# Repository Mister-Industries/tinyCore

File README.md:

# tinyCore - A Better Way to Learn ESP32

<div align="center">

</div>

ESP32-S3 chips are manufactured by Espressif®.
> Espressif® is a trademark of Espressif Systems (Shanghai) Co.Ltd (https://www.espressif.com/).

The tinyCore ESP32-S3 Board can be programmed with the Arduino® IDE.
> Arduino® is a trademark of Arduino LLC (https://www.arduino.cc/).

## Overview

tinyCore is an engineering learning platform based around an "open-knowledge" microcontroller board designed to help educate individuals on the world of advanced embedded systems. tinyCore’s mission is to bridge the gap between undergrad and industry, equipping young professionals with the resources they need to build their portfolio and bring their ideas to life. 

## Pinout

### Key Features

- **Processor**: ESP32-S3 Mini Dual-Core No-PSRAM
- **Connectivity**: 
  - WiFi & Bluetooth LE
  - USB-C
  - 2x STEMMA/QWIIC I2C Connectors
  - Micro SD Card Slot
  - Built-in LSM6DSO IMU
- **Power**: 
  - USB-C powered
  - LiPo battery support with charging circuit
  - Low power sleep modes, Dedicated I2C PWR Rail
- **Dimensions**: 50mm x 50mm

## Getting Started

Open up the "START-HERE.pdf" document, or check out [our documentation](https://docs.mr.industries) to get started.

## Purchase

If you would like to get a tinyCore for yourself, please [visit our website](https://mr.industries/tiny-core) to purchase one!

For professors, tax-exempt organizations, or bulk orders (>10), please contact us through the following email address:
[support@mr.industries](mailto:support@mr.industries)

## Hardware

The complete hardware design files are available in the [hardware folder](https://github.com/Mister-Industries/tinyCore/tree/main/Hardware), including:
- Schematic files 
- PCB layout files (Altium/KiCad format)
- Bill of Materials (BOM)
- Manufacturing files (Gerber)
- Assembly instructions

## Development

### Contributing

We welcome contributions! Please see our [Contributing Guide](CONTRIBUTING.md) for details on:
- Code style guidelines
- Development workflow
- Testing requirements
- Pull request process

## Community

- [Discord Server](https://discord.gg/hvJZhwfQsF)
- [Bluesky](https://bsky.app/profile/mr.industries)

## License

This project is licensed under the MIT License - see the [LICENSE](LICENSE) file for details.

## Acknowledgments
The tinyCore project thrives thanks to the generous support of our manufacturing and development partners:
### --- PCBWay ---

PCBWay provides exceptional PCB manufacturing services and has been instrumental in bringing tinyCore to life through their reliable prototyping capabilities. You can order our open-source designs directly from [their website](https://www.pcbway.com/project/shareproject/iota_The_Open_Source_Advanced_IoT_Learning_Platform_12776757.html)

Special thanks to:
- The Adafruit team for inspiration
- All of our open source contributors
- "Prof. Eric Bogatin, Prof. Chris Coulston, Tyler Watts, Chaz Havens and countless others who inspired me to create fantastic things." - Geoff M.

## Support

MR.INDUSTRIES offers comprehensive technical support for everyone in our tinyCommunity:

* Help with understanding documentation and setup challenges
* Replacement parts for defective components
* Expert guidance for your tinyCore projects
* Weekly "Office Hours" every Thursday at 4:30 MST on [Discord Server](https://discord.gg/hvJZhwfQsF)
  * Get 1-1 help from our engineers via Discord voice
* Active community support through our [Discord](https://discord.gg/hvJZhwfQsF)

## Star History

You can also send us an email to:
[support@mr.industries](mailto:support@mr.industries)

**Our team is committed to helping you succeed with your project every step of the way.**

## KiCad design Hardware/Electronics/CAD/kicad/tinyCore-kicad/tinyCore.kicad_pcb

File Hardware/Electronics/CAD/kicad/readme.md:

These files were automatically created by Kicad import from the orginal Altium project

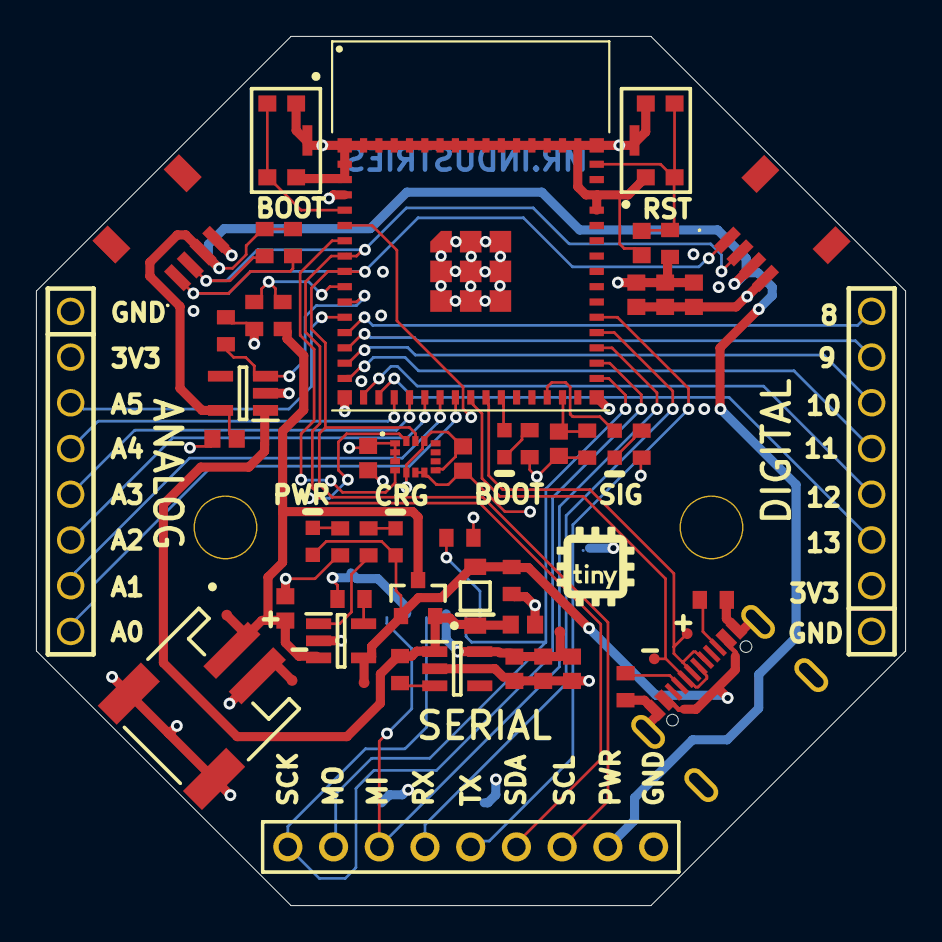
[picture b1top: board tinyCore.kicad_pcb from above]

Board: 4 copper layers, 48.3 x 48.3 mm, 57 parts (1 on the bottom side), 45 nets.

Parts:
B1: LSM6DS3TR
B2, B4: AP2112K-3.3TRG1; SOT95P270X145-5N
B3: MCP73831T-2ACI_OT; SOT95P270X145-5N
BOOT: HSMA-C190; AVAG-HSMX-C190_V
C1, C2, C3, C4, C7, C8, C9, C10, C11, C12, C13: Capacitor 10 uF +/- 0.25 uF 50 V 0603; CAPC1608X87X35NL15T15
C5, C6: Capacitor 0.1 uF 50 V 0603; CAPC1608X87X35NL15T15
CRG: HSMA-C190; AVAG-HSMX-C190_V
D1: MBR120; ONSC-SOD-123FL-2-498-01_V
J1: 2908-05WB-MG; FP-2908-05WB-MG-MFG
J2, J3: PPTC081LFBN-RC; 8_PIN_100MIL - Female
J4: HTSW-109-07-X-SJ; JM-9_HTSW-109-07-X-S
J5: USB4105-GF-A
J6, J7: 4208; 4390
P1: CN-1P-2M-R2; JST- S2B-PH-SM4-TB(LF)(SN)-2_V
PWR: HSMA-C190; AVAG-HSMX-C190_V
Q1: DMG2305UX-7; FP-SOT23-MFG
R1, R2, R7, R8, R9, R12: Resistor 100k +/-1% 0603 100 mW; RESC1608X55X25ML10T15
R3, R10, R13, R16, R17: Resistor 4.7k +/-1% 0603 100 mW; RESC1608X55X25ML10T15
R4, R5, R6, R11: Resistor 1k +/-1% 0603 100 mW; RESC1608X55X25ML10T15
R14, R15: Resistor 5.1k +/-1% 0603 100 mW; RESC1608X55X25ML10T15
SIG: HSMA-C190; AVAG-HSMX-C190_V
SW1, SW2: KMR211GLFS; FP-KMR211GLFS-MFG
TP1, TP2, TP3, TP4, TP5, TP6: TPAD6R; TP06R
U1: ESP32-S3-MINI-1-N8

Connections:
3V3: B1.5, B1.8, B1.12, B2.5, C1.2, C2.2, C3.2, C5.2, C6.2, C8.2, C9.2, C10.2, J1.4, J2.2, J3.2, R1.1, R3.1, TP3.1, U1.3
A0: J2.8, U1.22
A1: J2.7, U1.21
A2: J2.6, U1.20
A3: J2.5, U1.19
A4: J2.4, U1.18
A5: J2.3, U1.11
BOOT: SW1.3, SW1.4, U1.4
CHRG_STAT: B3.1, R11.2
CS: J1.2, R1.2, U1.5
D8: J3.8, U1.12
D9: J3.7, U1.13
D10: J3.6, U1.14
D11: J3.5, U1.15
D12: J3.4, U1.16
D13: J3.3, U1.17
D+: J5.A6, J5.B6, TP4.1, U1.24
D-: J5.A7, J5.B7, TP5.1, U1.23
EN: B2.3, R7.2
GND: B1.1, B1.2, B1.3, B1.6, B1.7, B2.2, B3.2, B4.2, C1.1, C2.1, C3.1, C4.1, C5.1, C6.1, C7.1, C8.1, C9.1, C10.1, C11.1, C12.1, C13.1, J1.6, J1.9, J1.10, J1.11, J1.12, J2.1, J3.1, J4.9, J5.A1B12, J5.B1A12, J5.M1, J5.M2, J5.M3, J5.M4, J6.1, J7.1, P1.2, P1.MP1, P1.MP2, R2.2, R4.2, R5.2, R6.2, R8.1, R10.2, R12.1, R13.1, R14.2, R15.2, SW1.1, SW1.2, SW1.5, SW2.1, SW2.2, SW2.5, TP6.1, U1.1, U1.2, U1.42, U1.43, U1.46, U1.47, U1.48, U1.49, U1.50, U1.51, U1.52, U1.53, U1.54, U1.55, U1.56, U1.57, U1.58, U1.59, U1.60, U1.61, U1.61_1, U1.61_2, U1.61_3, U1.61_4, U1.61_5, U1.61_6, U1.61_7, U1.61_8, U1.62, U1.63, U1.64, U1.65
I2C_PWR: B4.3, R13.2, U1.10
INT: B1.4, U1.6
LED1: BOOT.1, U1.25
LED2: SIG.1, U1.28
MISO: J1.7, J4.3, U1.33
MOSI: J1.3, J4.2, U1.31
NetB3_5: B3.5, R10.1
NetBOOT_2: BOOT.2, R5.1
NetC4_2: C4.2, R2.1, U1.29
NetCRG_2: CRG.2, R11.1
NetJ5_A5: J5.A5, R15.1
NetJ5_B5: J5.B5, R14.1
NetPWR_2: PWR.2, R4.1
NetR6_1: R6.1, SIG.2
RESET: C7.2, R3.2, SW2.3, SW2.4, U1.45
RX: J4.4, U1.34
SCK: J1.5, J4.1, U1.32
SCL: B1.13, J4.7, J6.4, J7.4, R17.2, U1.8
SDA: B1.14, J4.6, J6.3, J7.3, R16.2, U1.7
TX: J4.5, U1.35
VBAT: B3.3, C12.2, P1.1, Q1.3, R9.2, TP1.1
VBUS: B3.4, CRG.1, D1.2, J5.A4B9, J5.B4A9, PWR.1, Q1.1, R8.2, TP2.1
VDIV: R9.1, R12.2, U1.9
VHI: B2.1, B4.1, C11.2, D1.1, Q1.2, R7.1
VSENSOR: B4.5, C13.2, J4.8, J6.2, J7.2, R16.1, R17.1

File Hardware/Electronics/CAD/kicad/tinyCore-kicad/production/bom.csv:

Designator,Footprint,Quantity,Value,LCSC Part #
"_2, ",,2,,
B1,LSM6DS3TR,1,LSM6DS3TR,
"B2, B4",SOT95P270X145-5N,2,AP2112K-3.3TRG1,
B3,SOT95P270X145-5N,1,MCP73831T-2ACI_OT,
"BOOT, CRG, PWR, SIG",AVAG-HSMX-C190_V,4,HSMA-C190,
"C1, C10, C11, C12, C13, C2, C3, C4, C7, C8, C9",CAPC1608X87X35NL15T15,11,Capacitor 10 uF +/- 0.25 uF 50 V 0603,
"C5, C6",CAPC1608X87X35NL15T15,2,Capacitor  0.1 uF 50 V 0603,
D1,ONSC-SOD-123FL-2-498-01_V,1,MBR120,
J1,FP-2908-05WB-MG-MFG,1,2908-05WB-MG,
"J2, J3",8_PIN_100MIL - Female,2,PPTC081LFBN-RC,
J4,JM-9_HTSW-109-07-X-S,1,HTSW-109-07-X-SJ,
J5,USB4105-GF-A,1,USB4105-GF-A,
"J6, J7",4390,2,4208,
P1,JST- S2B-PH-SM4-TB(LF)(SN)-2_V,1,CN-1P-2M-R2,
Q1,FP-SOT23-MFG,1,DMG2305UX-7,
"R1, R12, R2, R7, R8, R9",RESC1608X55X25ML10T15,6,Resistor 100k +/-1% 0603 100 mW,
"R10, R13, R16, R17, R3",RESC1608X55X25ML10T15,5,Resistor 4.7k +/-1% 0603 100 mW,
"R11, R4, R5, R6",RESC1608X55X25ML10T15,4,Resistor 1k +/-1% 0603 100 mW,
"R14, R15",RESC1608X55X25ML10T15,2,Resistor 5.1k +/-1% 0603 100 mW,
"SW1, SW2",FP-KMR211GLFS-MFG,2,KMR211GLFS,
"TP1, TP2, TP3, TP4, TP5, TP6",TP06R,6,TPAD6R,
U1,ESP32-S3-MINI-1-N8,1,ESP32-S3-MINI-1-N8,

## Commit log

2024-11-08 Added files from Rev 1.0 and Arduino example files for I2C, IMU, and Analog Outputs
2024-11-08 Update README.md
    ai generated rough draft. Information not accurate.
2024-11-24 Added Arduino Examples and image assets
2024-11-24 Updated logo
2024-11-24 Removed logo
2024-11-24 Adds logo.png
2024-11-24 Updates README
2024-12-31 Adds Rev 2.0 Board design and assets directory
2025-01-27 updated software and changed naming conventions to "tiny"
2025-02-21 Adds Enclosure Files
2025-03-22 Cleaned up File Org. and Updated CAD files.
2025-03-22 Adds images
2025-03-22 Updates main Photos/tinyCore-4Colors.png
2025-03-23 Updates Photos again.
2025-03-23 Adds Pinout
2025-03-23 Updates Pin Legend
2025-03-23 Updated Datasheets and added draft tinyCore V2 Datasheet
2025-03-23 Rename tinyCore Datasheet (V2).pdf to tinyCore Datasheet (V2) DRAFT.pdf
2025-03-27 Updates images
2025-06-10 Updates the README image
2025-06-14 Update README.md
    Adds star history
2025-08-21 Adds new revision of datasheet
2025-08-21 Renamed Rev 2 to update the correct file
2025-09-09 Updates Start-Here PDF
2025-12-02 Updated the tinyCore Datasheet to V2.1
2025-12-19 Add readme for Kicad files from Altium project
2025-12-19 Add auto import Kicad and gerbers
2026-02-21 Updates MACAddress example
2026-02-21 Added new images for V2.1

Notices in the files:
README.md:
License: MIT
